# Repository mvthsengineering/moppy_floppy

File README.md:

# moppy_floppy
This is a musical floppy drive

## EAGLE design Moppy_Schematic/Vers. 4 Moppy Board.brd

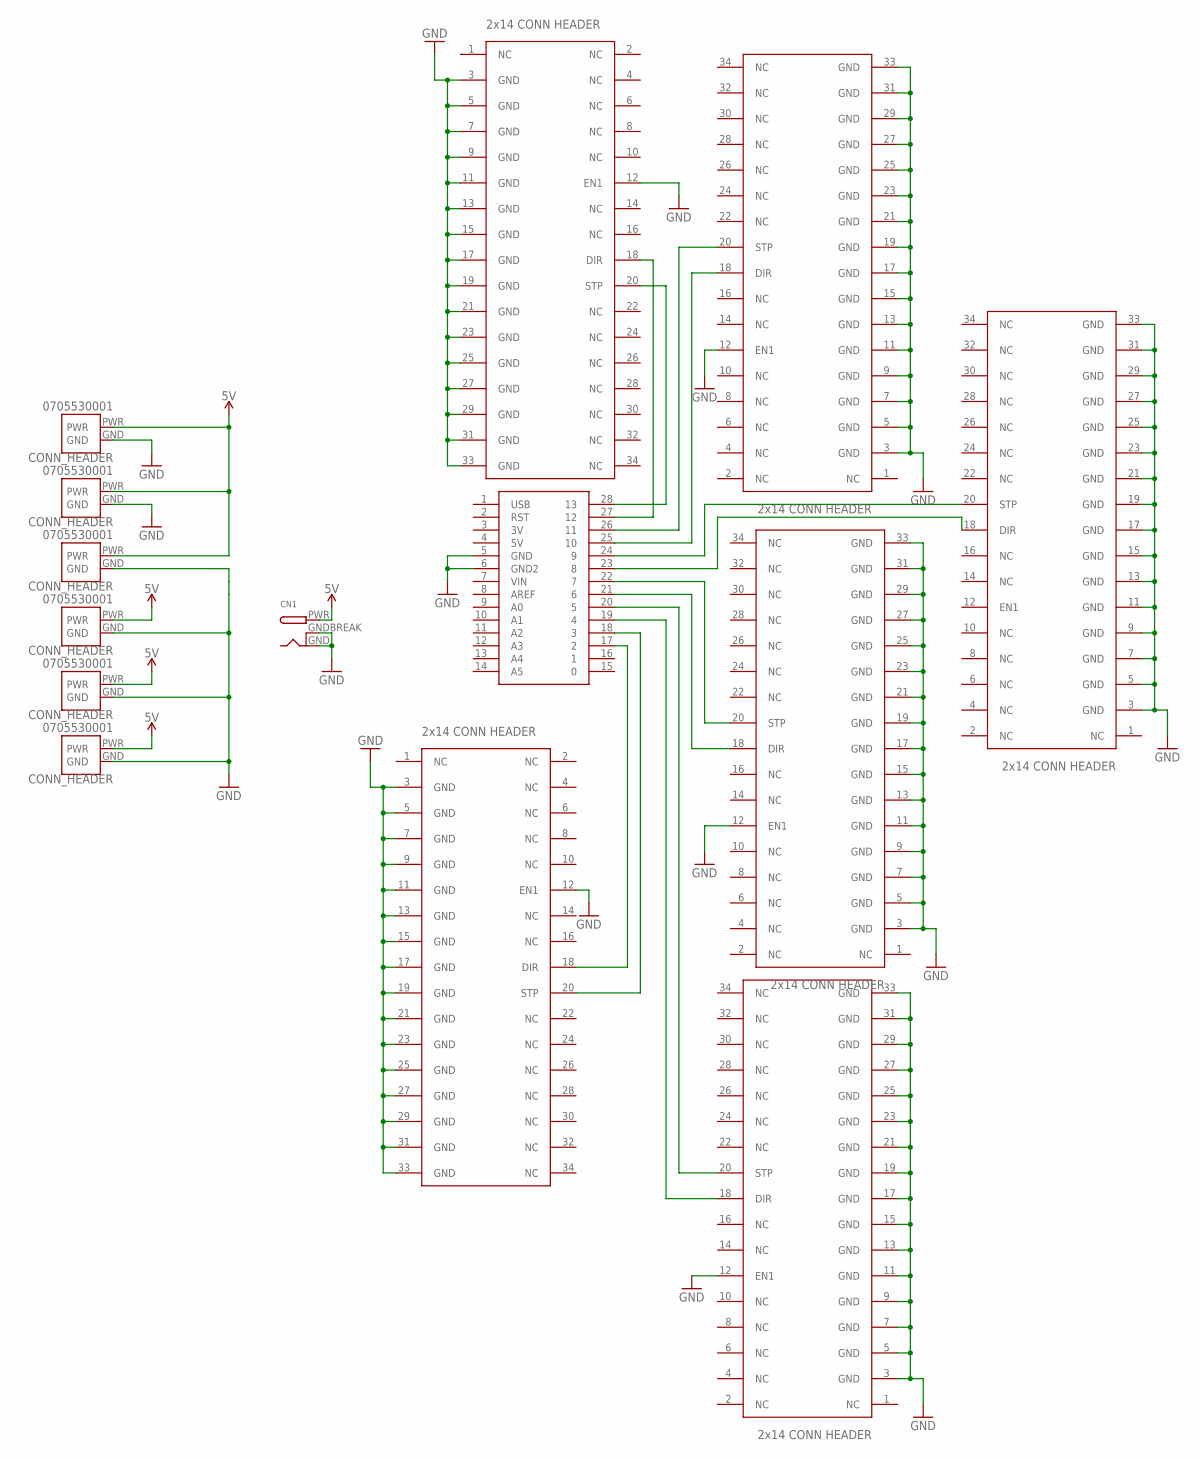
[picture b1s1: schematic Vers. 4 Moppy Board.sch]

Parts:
CN1: DCBARRELPTH; DCJACK_2MM_PTH
U$1, U$2, U$3, U$4, U$5, U$6: 2X14_CONN_HEADER; 2X17_CONN_HEADER
U$8: METROMINI
X1, X2, X3, X4, X5, X6: 0705530001; MOLEX_0705530001

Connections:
5V: CN1.PWR, X1.PWR, X2.PWR, X3.PWR, X4.PWR, X5.PWR, X6.PWR
GND: CN1.GND, CN1.GNDBREAK, U$1.3 (GND), U$1.5 (GND), U$1.7 (GND), U$1.9 (GND), U$1.11 (GND), U$1.12 (EN1), U$1.13 (GND), U$1.15 (GND), U$1.17 (GND), U$1.19 (GND), U$1.21 (GND), U$1.23 (GND), U$1.25 (GND), U$1.27 (GND), U$1.29 (GND), U$1.31 (GND), U$1.33 (GND), U$2.3 (GND), U$2.5 (GND), U$2.7 (GND), U$2.9 (GND), U$2.11 (GND), U$2.12 (EN1), U$2.13 (GND), U$2.15 (GND), U$2.17 (GND), U$2.19 (GND), U$2.21 (GND), U$2.23 (GND), U$2.25 (GND), U$2.27 (GND), U$2.29 (GND), U$2.31 (GND), U$2.33 (GND), U$3.3 (GND), U$3.5 (GND), U$3.7 (GND), U$3.9 (GND), U$3.11 (GND), U$3.12 (EN1), U$3.13 (GND), U$3.15 (GND), U$3.17 (GND), U$3.19 (GND), U$3.21 (GND), U$3.23 (GND), U$3.25 (GND), U$3.27 (GND), U$3.29 (GND), U$3.31 (GND), U$3.33 (GND), U$4.3 (GND), U$4.5 (GND), U$4.7 (GND), U$4.9 (GND), U$4.11 (GND), U$4.12 (EN1), U$4.13 (GND), U$4.15 (GND), U$4.17 (GND), U$4.19 (GND), U$4.21 (GND), U$4.23 (GND), U$4.25 (GND), U$4.27 (GND), U$4.29 (GND), U$4.31 (GND), U$4.33 (GND), U$5.3 (GND), U$5.5 (GND), U$5.7 (GND), U$5.9 (GND), U$5.11 (GND), U$5.12 (EN1), U$5.13 (GND), U$5.15 (GND), U$5.17 (GND), U$5.19 (GND), U$5.21 (GND), U$5.23 (GND), U$5.25 (GND), U$5.27 (GND), U$5.29 (GND), U$5.31 (GND), U$5.33 (GND), U$6.3 (GND), U$6.5 (GND), U$6.7 (GND), U$6.9 (GND), U$6.11 (GND), U$6.13 (GND), U$6.15 (GND), U$6.17 (GND), U$6.19 (GND), U$6.21 (GND), U$6.23 (GND), U$6.25 (GND), U$6.27 (GND), U$6.29 (GND), U$6.31 (GND), U$6.33 (GND), U$8.5 (GND), U$8.6 (GND2), X1.GND, X2.GND, X3.GND, X4.GND, X5.GND, X6.GND
unnamed: U$2.20 (STP), U$8.28 (13)
unnamed: U$2.18 (DIR), U$8.27 (12)
unnamed: U$3.20 (STP), U$8.26 (11)
unnamed: U$3.18 (DIR), U$8.25 (10)
unnamed: U$5.20 (STP), U$8.22 (7)
unnamed: U$5.18 (DIR), U$8.21 (6)
unnamed: U$1.18 (DIR), U$8.17 (2)
unnamed: U$4.18 (DIR), U$8.19 (4)
unnamed: U$1.20 (STP), U$8.18 (3)
unnamed: U$6.20 (STP), U$8.24 (9)
unnamed: U$4.20 (STP), U$8.20 (5)
unnamed: U$6.18 (DIR), U$8.23 (8)

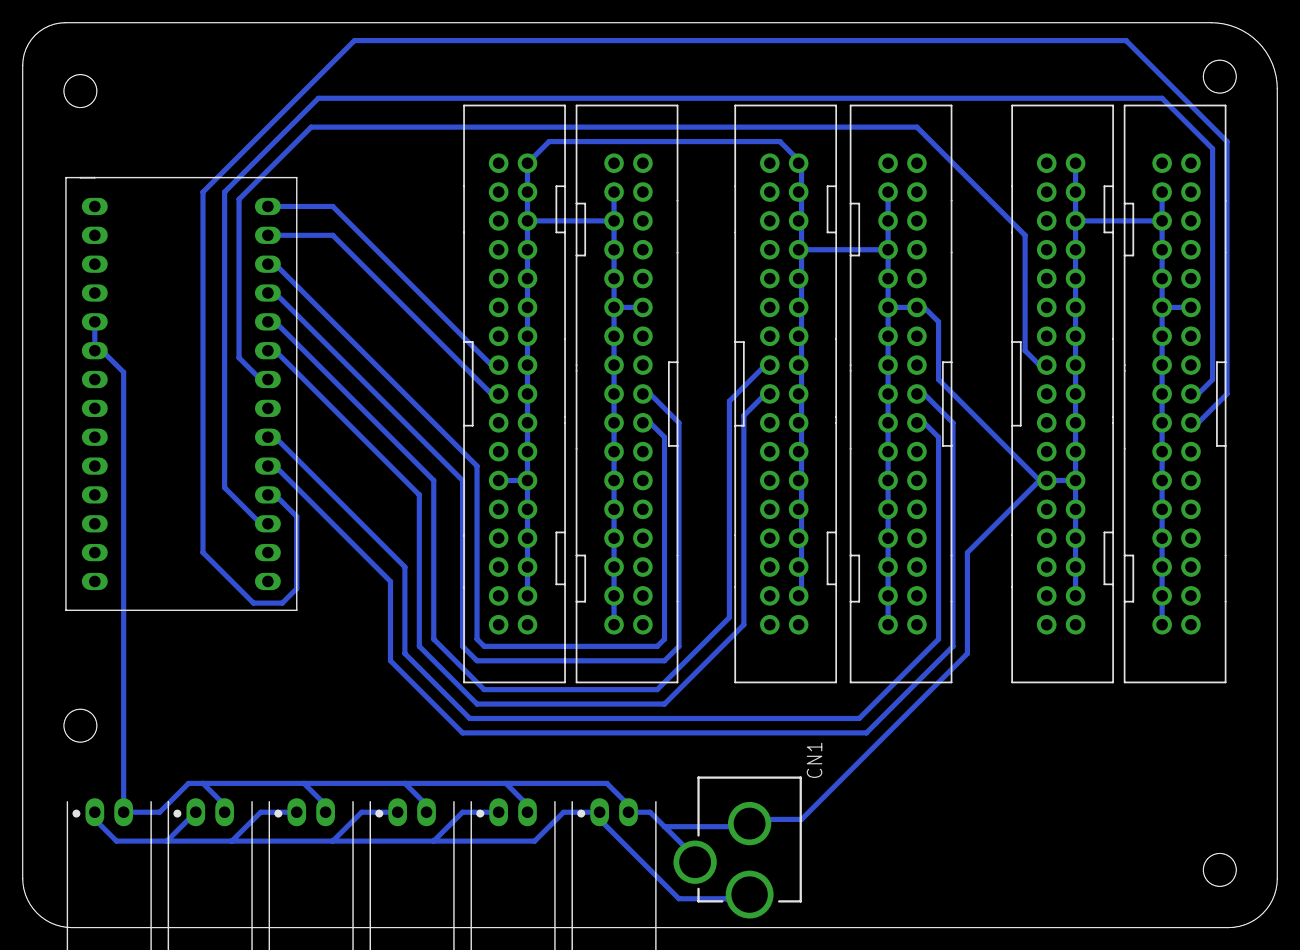
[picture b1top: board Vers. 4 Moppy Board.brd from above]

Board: 2 copper layers, 110.5 x 79.7 mm, 14 parts (0 on the bottom side), 14 nets.

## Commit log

2019-04-25 First Commit!
    not to college though
2019-04-25 Schematics
    :)

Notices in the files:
parts and their libraries:
SparkFun-PowerSymbols: Licensing: Creative Commons ShareAlike 4.0 International - https://creativecommons.org/licenses/by-sa/4.0
